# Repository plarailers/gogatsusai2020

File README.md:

# 第93回五月祭

## インストール
```
git clone https://github.com/plarailers/gogatsusai2020.git
```

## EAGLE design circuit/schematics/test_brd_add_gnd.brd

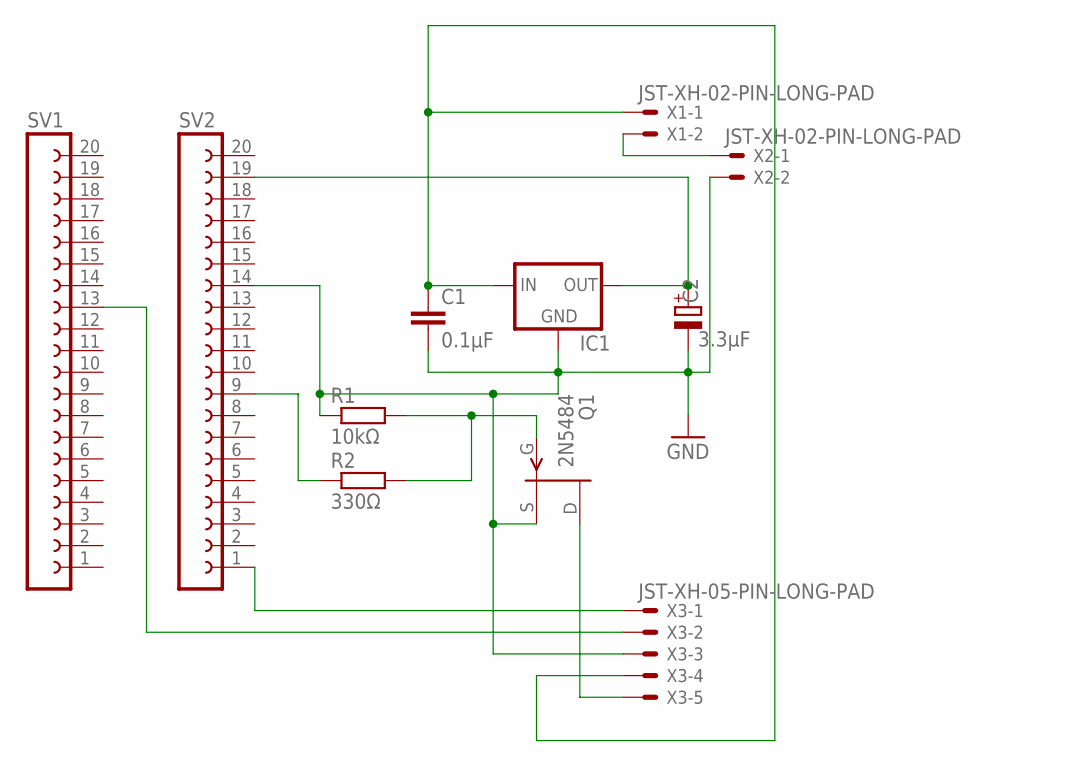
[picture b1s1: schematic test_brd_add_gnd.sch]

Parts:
C1: 0.1μF; C025-040X050
C2: 3.3μF; E2,5-5
IC1: 78XXS
Q1: 2N5484; TO92-
R1: 10kΩ; 0207/10
R2: 330Ω; 0207/10
SV1, SV2: FE20-1; FE20
X1, X2: JST-XH-02-PIN-LONG-PAD; JST-XH-02-PACKAGE-LONG-PAD
X3: JST-XH-05-PIN-LONG-PAD; JST-XH-05-PACKAGE-LONG-PAD

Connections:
GND: C1.2, C2.-, IC1.GND, Q1.2 (S), R1.1, SV2.14, X2.2, X3.3
unnamed: C1.1, IC1.IN, X1.1, X3.4
unnamed: C2.+, IC1.OUT, SV2.19
unnamed: Q1.1 (G), R1.2, R2.2
unnamed: R2.1, SV2.9
unnamed: X1.2, X2.1
unnamed: SV2.1, X3.1
unnamed: SV1.13, X3.2
unnamed: Q1.3 (D), X3.5

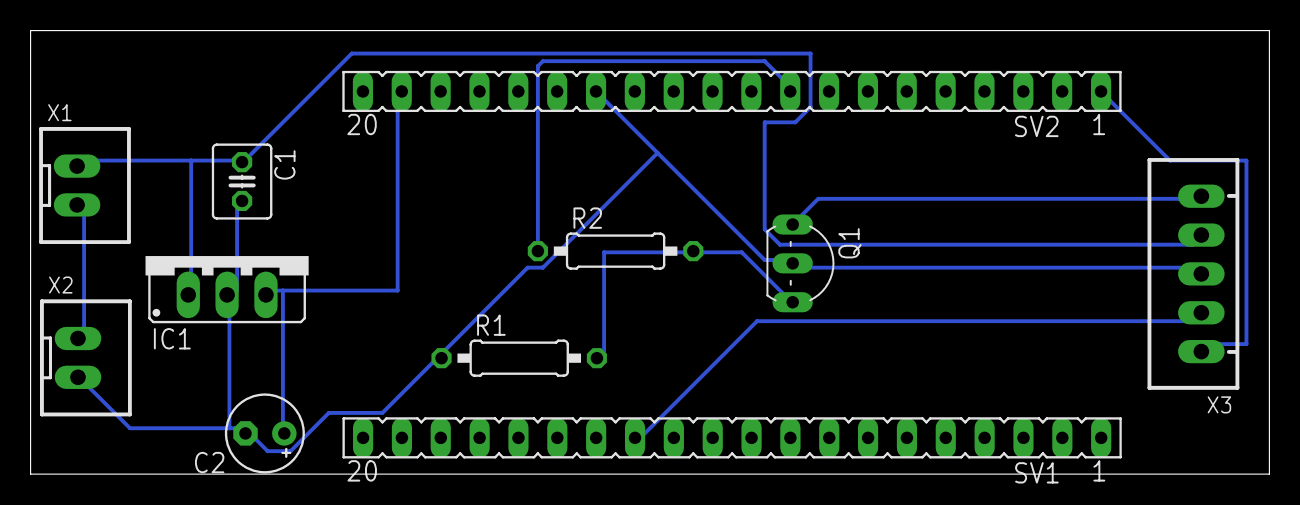
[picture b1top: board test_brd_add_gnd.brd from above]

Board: 2 copper layers, 81.0 x 29.0 mm, 11 parts (0 on the bottom side), 9 nets.

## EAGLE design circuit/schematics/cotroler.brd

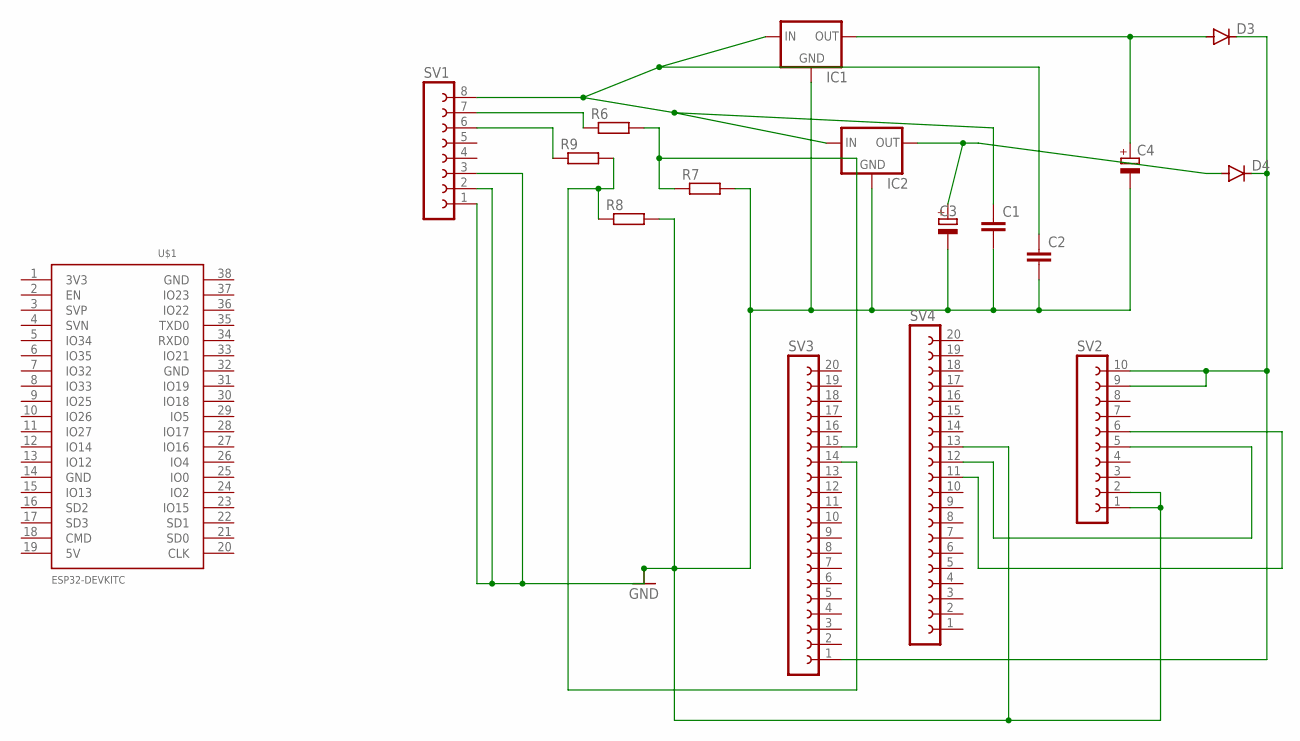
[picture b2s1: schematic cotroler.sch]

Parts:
C1, C2: C-EU025-024X044; C025-024X044
C3, C4: CPOL-EUE2.5-5; E2,5-5
D3, D4: DIODE-D-10; D-10
IC1, IC2: 78XXS
R6, R7, R8, R9: R-EU_0207/10; 0207/10
SV1: FE08-1; FE08
SV2: FE10-1; FE10
SV3, SV4: FE20-1; FE20
U$1: ESP32DEVKITC; ESP32-DEVKITC

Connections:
GND: C1.2, C2.2, C3.-, C4.-, IC1.GND, IC2.GND, R7.2, R8.2, SV1.1, SV1.2, SV1.3, SV2.1, SV2.2, SV4.13, U$1.19 (5V), U$1.38 (GND)
unnamed: R6.1, SV1.7
unnamed: SV2.5, SV4.12
unnamed: C1.1, C2.1, IC1.IN, IC2.IN, SV1.8
unnamed: R6.2, R7.1, SV3.15
unnamed: R9.1, SV1.6
unnamed: R8.1, R9.2, SV3.14
unnamed: C3.+, D4.A, IC2.OUT
unnamed: C4.+, D3.A, IC1.OUT
unnamed: SV2.6, SV4.11
unnamed: D3.C, D4.C, SV2.9, SV2.10, SV3.1

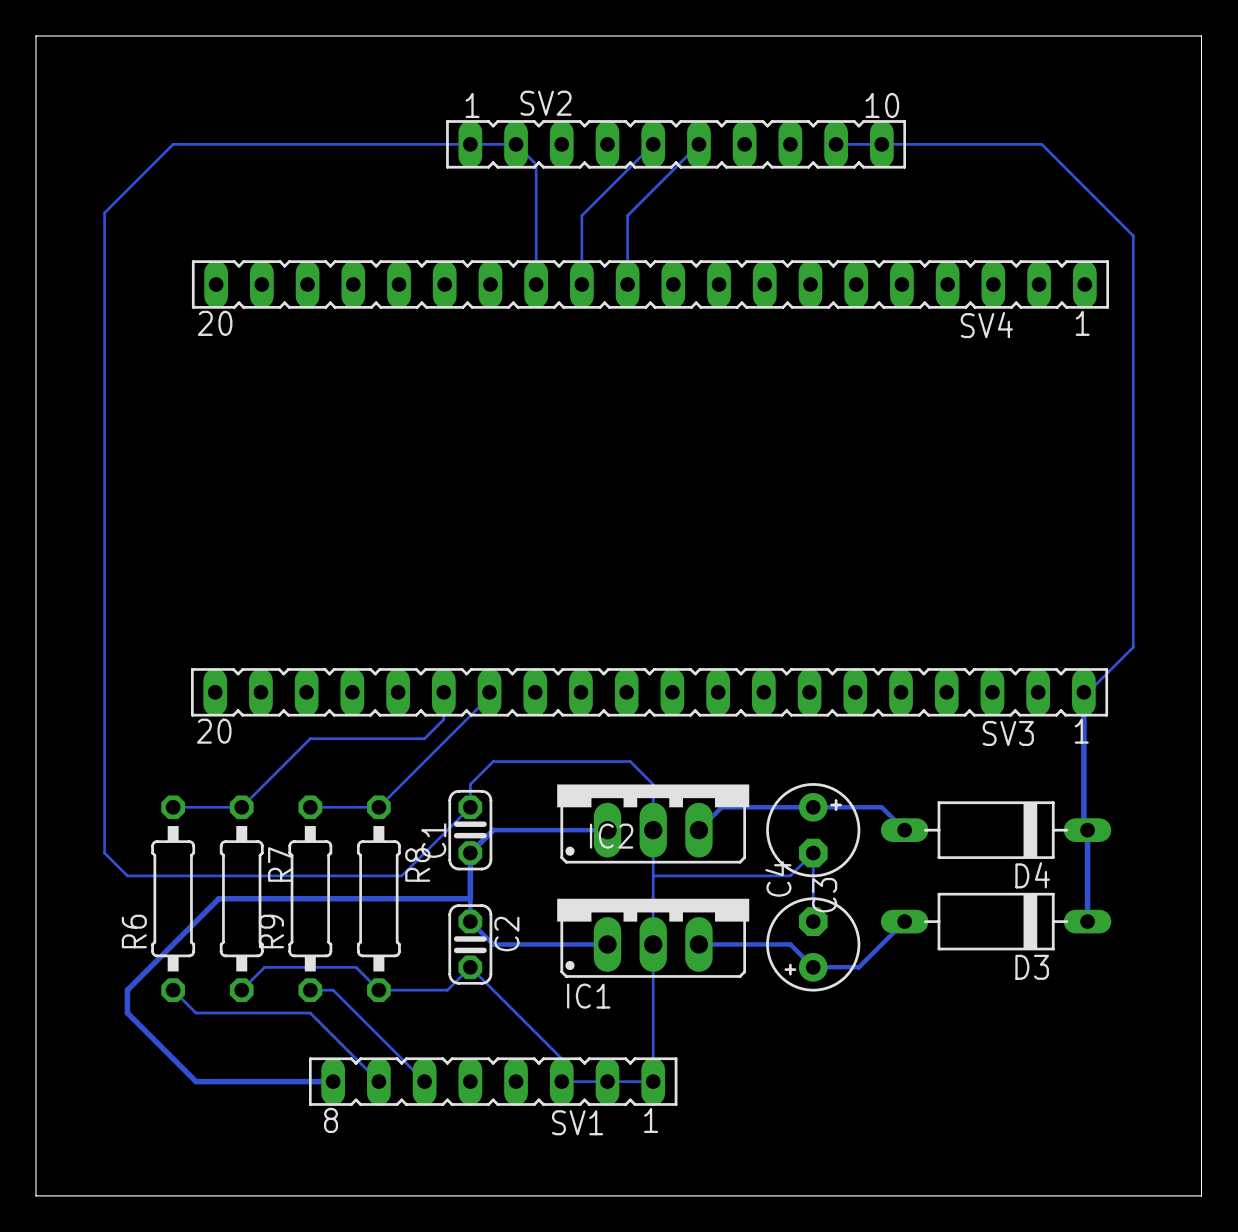
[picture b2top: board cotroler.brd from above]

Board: 2 copper layers, 64.8 x 64.4 mm, 16 parts (0 on the bottom side), 11 nets.

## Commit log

2020-02-16 Add files via upload
    描画のデモコード
2020-02-16 Rename test.pde to discribe.pde
2020-02-16 Bluetooth通信 by akiyama
2020-02-16 hole_sensor
2020-02-25 PID制御
2020-02-26 train_esp32
2020-02-26 pc.pde
2020-03-05 Update Display.pde
    パーセンテージで表示できるように変更
2020-03-05 Update Display.pde
    class Displayに変更してインデントを入れた
2020-03-05 Update Display.pde
    セミコロン抜けと全角スペースの排除
2020-03-05 Update Display.pde
    線路と電車のずれを修正
2020-03-05 Add 時刻表（仮）
2020-03-05 RAISE 3D PRO2使い方
2020-03-07 Add ESP32
2020-03-07 Create Display2
2020-03-07 Rename Display2 to Display2.pde
2020-03-07 Move class State
2020-03-07 Add Train.move
2020-03-07 Add Junction
2020-03-07 Add ポイント切り替え（仮）
2020-03-07 ESP32 の挙動をシミュレーション
2020-03-07 駅を設置
2020-03-07 Rename Display2.pde to Display.pde
2020-03-07 Change train to trainList
2020-03-07 配列に対応
2020-03-07 複数車両を動かす
2020-03-07 複数列車を独立に動かす
2020-03-17 Lv.4先行列車と分岐器の考慮(ダイヤ機能はまだ)
2020-03-19 Lv.4 Display added
2020-03-19 制御を完全にOperationへ分離
2020-03-19 Add Communication
2020-03-19 Change state.esp32 to communication
2020-03-19 Update Communication
2020-03-28 targetSpeed算出に対応
2020-04-12 targetSpeed算出に対応、軽微な修正
2020-04-12 古いファイルを削除
2020-04-12 ファイル名変更
2020-04-14 test
2020-04-17 センサを実装
2020-04-18 Create test
2020-04-18 ESP32 got located.
2020-04-18 renamed
2020-04-22 add some parts
2020-04-25 dekita
2020-04-30 ボード図用のフォルダ作成
2020-04-30 gridを表示
2020-05-02 ベタを作成
2020-05-02 GNDを追加
2020-05-02 ピンソケ動かし厳禁
2020-05-09 整理された配線
2020-05-16 暫定管制版
2020-05-23 制御盤の回路
2020-07-17 drc cleared
2020-07-18 ベタ塗り
2020-07-18 小野が試行
2020-08-01 webコントローラUIを作成
2020-08-01 WebSocketのバックエンド
2020-08-01 bluetoothのテストをしたい
2020-08-02 serial通信のサンプルコード(参考: qiita-シリアル通信入門【Python】)
2020-08-02 PW入力欄を追加
2020-08-02 パスワード機能
2020-08-02 エラーコードの追加
2020-08-02 パスワードの有効期限の情報をレスポンスに含める
2020-08-02 web経由でのリモコンからの入力をespに送るためのプログラム(未完成)
2020-08-02 websocketに対応
2020-08-02 ミスの修正
2020-08-02 PW照合機能を追加
2020-08-03 Update train_esp32_test.ino
    始動処理実装
2020-08-03 始動処理追加
2020-08-03 websocketからspeedを取り込んでesp32に渡すプログラム
2020-08-03 修正しました
2020-08-03 目標値の入力による速度制御に対応させたつもり
2020-08-03 ポインタ直した
2020-08-03 使わないファイルを削除
2020-08-03 余分な部分を一部消しました。
2020-08-03 コントローラhtmlの微修正
2020-08-03 1を押すとint10を送信できるようにした(テスト用)
2020-08-03 シリアル通信で送られてきた数値を元にサーボを動かすプログラム(cdsのデータ送るのは未実装)
2020-08-03 通信部分
2020-08-03 ESP32とArduinoとの通信
2020-08-03 説明を追加
2020-08-03 CdSからの情報をPCに送る部分のコードを追加。手元でコンパイルが通ることを確認。
2020-08-03 READMEを追加
2020-08-04 Arduinoからの信号を受け取る処理
2020-08-04 Varspeedservoサンプルコード
2020-08-04 サーボやCdSが増えても大丈夫なように変更(コンパイルは通る)
2020-08-04 信号が何も来ていない時にセンサーの読み取りをしない気がしたので直しました。
2020-08-04 ミスがあったので直しました。
2020-08-04 バグになりそうなところがあったので修正しました
2020-08-04 CdSセンサーの読み取りのタイミングを少し変えました(実機で試さないとなんとも家無さそう)。
2020-08-04 コメント追加。
2020-08-04 車両からの信号を処理
2020-08-04 ミスを直しました。
2020-08-04 複数のESP32との通信に対応
2020-08-04 controller.htmlを修正
2020-08-04 start関数のコメントアウト(これでリモコンからの信号通りに動くようになりました。)
2020-08-04 controllerの修正
2020-08-04 start関数をコメントアウト
2020-08-04 テスト用 2駅1車両5セクション
2020-08-04 2駅1車両のテストに対応
2020-08-04 コメントの追加
2020-08-05 サーボ1、センサー2に対応したコードにしました。Pinの位置など適宜変えてください。
2020-08-05 バグ修正
2020-08-05 母艦となるArduinoMega用のコード(子艦にはcom_to_arduinoが使いまわせるはず)
2020-08-05 少し書き方を変えました、昨日は同じです
2020-08-05 コメント追加
2020-08-05 servoSpeed=5だとセンサのバグなし
2020-08-06 センサーの値からの判別を差分ではなく基準値を設けて判定する方法に変更。
2020-08-06 バグ修正(コンパイルが通るようになった。)
2020-08-06 サーボ0、センサーを一つA0につなげる場合のコードに書き換え(テスト用)
2020-08-06 テスト用に書き換えました。
2020-08-06 最初にbaselineを状況に応じて変更する仕様に変更
2020-08-06 time_for_passingを定義していたのに使っていなかったので使いました。挙動は変化なしです
2020-08-06 CdS_processを一部コメントアウトしておきました。
2020-08-06 母艦+センサ2つで動作確認済
2020-08-06 不要なファイル ESP32.pde と Figure.png を削除
2020-08-07 PIDのパラメータを調整
2020-08-07 動作確認済みのArduinoの設定
2020-08-07 セクションの長さを調節
2020-08-07 実機モードにArduinoを追加
2020-08-07 車両が車輪の１回転ごとに進んだ距離を送る
2020-08-08 ポイント切り替えなしに変更
2020-08-08 線形を若干変更
2020-08-08 速度を送り返す部分をコメントアウト
2020-08-08 8/8午前に動作確認済
2020-08-09 テスト用(8/9)
2020-08-09 Revert "ポイント切り替えなしに変更"
    This reverts commit b2d2e7ab5cd8943fad90c14eee4fd686eb21bd56.
2020-08-14 二駅二両用のコード(いじる必要あり)
2020-08-14 二駅二両用の時刻表(コピペしただけなのでいじる必要あり)
2020-08-14 時刻表変更
2020-08-14 サーボの向きを初期化できるように変更
2020-08-16 送受信時のログを調整
2020-08-16 start関数周りを調整し始動改善
2020-08-16 サーボの状態をシミュレーション側で保持
2020-08-16 サーボへの通信データに向きの情報も入れるように変更
2020-08-16 ポート接続時にOSを判別
2020-08-16 始動時の過回転を改善
2020-08-16 Bluetoothデバイス名とCOMポート名を対応付ける関数（Windows用）
2020-08-20 speed指令値を20～50に限定
2020-08-20 USBデバイス名とCOMポート名を対応付ける関数（Windows用）
2020-08-20 Bluetoothデバイス名とCOMポート名を対応付けるPythonスクリプト
2020-08-20 ログを詳細化
2020-08-20 Bluetooth接続時にOSを判別
2020-08-21 ライブ配信用のライブラリ
2020-08-21 不要な機能を削除
2020-08-21 不要な部分を削除
2020-08-21 配信側のコード
2020-08-22 inputを直に指定して動く車両側のコード
2020-08-22 グローバルにエクスポート
2020-08-22 車両側でPID制御しない！
2020-08-22 ライブストリーミング配信／視聴用のテストページを作成
2020-08-22 Trickle ICE を使用して接続を高速化
2020-08-22 pc_changableでポートを自動で選択（Windows用）
2020-08-24 配信／視聴用ライブラリの環境を修正
2020-08-24 speedは0～255の範囲で送る
2020-08-24 ライブラリの仕様変更
2020-08-24 gitignore
2020-08-24 自動運転コントローラに映像を組み込む
2020-08-24 コントローラ微修正、不要なファイルの削除
2020-08-24 live-streamingの説明を修正
2020-09-12 軽微な修正
2020-09-14 PID制御を実装
2020-09-14 controller.html → index.html
2020-09-14 アクセスキーをクエリパラメータで受け取る（要検討）
2020-09-15 master.start() に constraints を渡せるように変更
2020-09-15 配信者用画面を作成
2020-09-15 フォルダ名変更
2020-09-15 パスワード管理画面を作成
2020-09-16 パスワード生成用スクリプト
2020-09-16 開始時刻順でソート
2020-09-16 テストを追加
2020-09-16 パスワードの追加・削除を実装
2020-09-16 レバーのUI変更
2020-09-16 説明動画の埋め込み
2020-09-17 webrtc-adapter を使用（Safari 対策）
2020-09-19 Hide the password
2020-09-19 WebSocketの接続手順を変更
2020-09-19 前面展望埋め込み用のページを作成
2020-09-20 User Agent を含める
2020-09-21 Bump node-fetch from 2.6.0 to 2.6.1 in /backend
    Bumps [node-fetch](https://github.com/bitinn/node-fetch) from 2.6.0 to 2.6.1.
    - [Release notes](https://github.com/bitinn/node-fetch/releases)
    - [Changelog](https://github.com/node-fetch/node-fetch/blob/master/docs/CHANGELOG.md)
    - [Commits](https://github.com/bitinn/node-fetch/compare/v2.6.0...v2.6.1)
2020-09-21 Bump bl from 4.0.2 to 4.0.3 in /backend
    Bumps [bl](https://github.com/rvagg/bl) from 4.0.2 to 4.0.3.
    - [Release notes](https://github.com/rvagg/bl/releases)
    - [Commits](https://github.com/rvagg/bl/compare/v4.0.2...v4.0.3)
2020-10-17 PIDのinputの更新の仕方を改訂
2020-12-13 Bump ini from 1.3.5 to 1.3.8 in /backend
    Bumps [ini](https://github.com/isaacs/ini) from 1.3.5 to 1.3.8.
    - [Release notes](https://github.com/isaacs/ini/releases)
    - [Commits](https://github.com/isaacs/ini/compare/v1.3.5...v1.3.8)
